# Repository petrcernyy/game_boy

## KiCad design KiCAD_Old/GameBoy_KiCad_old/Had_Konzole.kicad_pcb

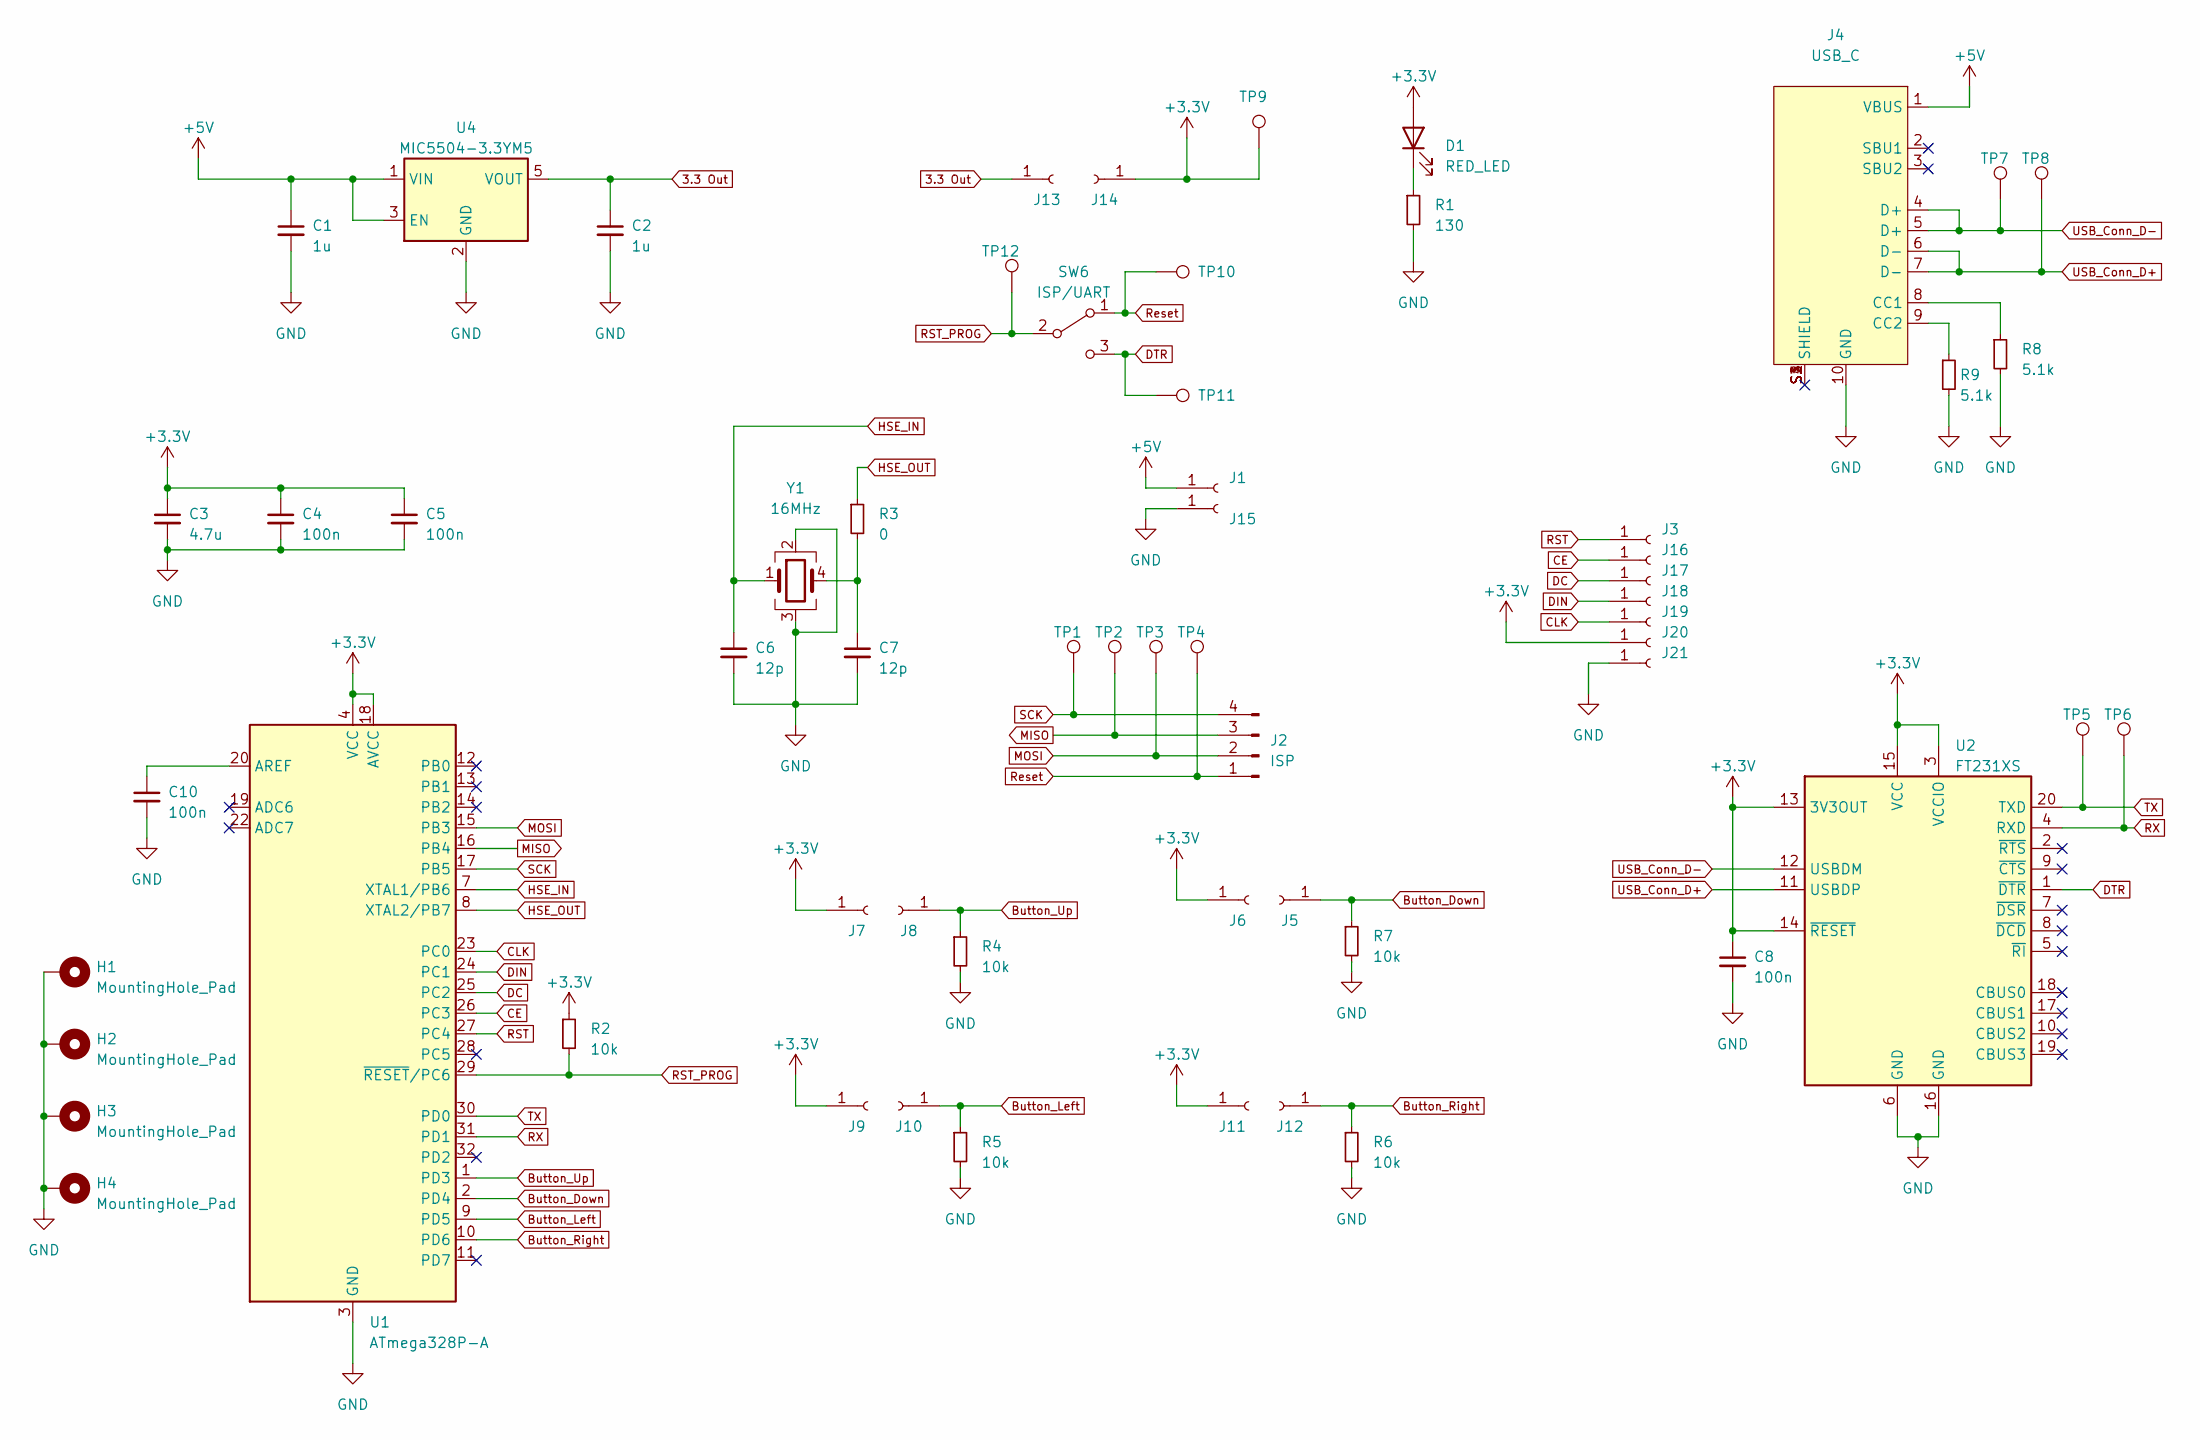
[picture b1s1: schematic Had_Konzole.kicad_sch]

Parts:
C1, C2: 1u; C_0603_1608Metric
C3: 4.7u; C_0603_1608Metric
C4, C5, C8, C10: 100n; C_0603_1608Metric
C6, C7: 12p; C_0603_1608Metric
D1: RED_LED; LED_D5.0mm_Horizontal_O1.27mm_Z3.0mm
H1, H2, H3, H4: MountingHole_Pad; MountingHole_3.2mm_M3_Pad
J1: 5V; TestPoint_Pad_D2.0mm
J2: ISP; Conn_01x04_90
J3: RST; TestPoint_Pad_D2.0mm
J4: USB_C; USB480003A
J5: D; TestPoint_Pad_D2.0mm
J6, J7, J9, J11, J14, J20: 3V3; TestPoint_Pad_D2.0mm
J8: U; TestPoint_Pad_D2.0mm
J10: L; TestPoint_Pad_D2.0mm
J12: R; TestPoint_Pad_D2.0mm
J13: 3V3_O; TestPoint_Pad_D2.0mm
J15, J21: GND; TestPoint_Pad_D2.0mm
J16: CE; TestPoint_Pad_D2.0mm
J17: DC; TestPoint_Pad_D2.0mm
J18: DIN; TestPoint_Pad_D2.0mm
J19: CLK; TestPoint_Pad_D2.0mm
R1: 130; R_0603_1608Metric
R2, R4, R5, R6, R7: 10k; R_0603_1608Metric
R3: 0; R_0603_1608Metric
R8, R9: 5.1k; R_0603_1608Metric
SW6: ISP/UART; SPDT_switch
TP1, TP2, TP3, TP4, TP5, TP6, TP7, TP8, TP9, TP10, TP11, TP12: TestPoint; TestPoint_Pad_D2.0mm
U1: ATmega328P-A; TQFP-32_7x7mm_P0.8mm
U2: FT231XS; SSOP-20_3.9x8.7mm_P0.635mm
U4: MIC5504-3.3YM5; SOT-23-5
Y1: 16MHz; Crystal_SMD_3225-4Pin_3.2x2.5mm

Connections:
3.3 Out: C2.1, J13.1, U4.5 (VOUT)
+3V3: C3.1, C4.1, C5.1, C8.1, D1.2 (A), J6.1, J7.1, J9.1, J11.1, J14.1, J20.1, R2.1, TP9.1, U1.4 (VCC), U1.6 (VCC), U1.18 (AVCC), U2.3 (VCCIO), U2.13 (3V3OUT), U2.14 (~RESET), U2.15 (VCC)
+5V: C1.1, J1.1, J4.1 (VBUS), U4.1 (VIN), U4.3 (EN)
Button_Down: J5.1, R7.1, U1.2 (PD4)
Button_Left: J10.1, R5.1, U1.9 (PD5)
Button_Right: J12.1, R6.1, U1.10 (PD6)
Button_Up: J8.1, R4.1, U1.1 (PD3)
CE: J16.1, U1.26 (PC3)
CLK: J19.1, U1.23 (PC0)
DC: J17.1, U1.25 (PC2)
DIN: J18.1, U1.24 (PC1)
DTR: SW6.3 (C), TP11.1, U2.1 (~DTR)
GND: C1.2, C2.2, C3.2, C4.2, C5.2, C6.2, C7.2, C8.2, C10.2, H1.1, H2.1, H3.1, H4.1, J4.10 (GND), J15.1, J21.1, R1.2, R4.2, R5.2, R6.2, R7.2, R8.2, R9.2, U1.3 (GND), U1.5 (GND), U1.21 (GND), U2.6 (GND), U2.16 (GND), U4.2 (GND), Y1.2, Y1.3
HSE_IN: C6.1, U1.7 (XTAL1/PB6), Y1.1
HSE_OUT: R3.1, U1.8 (XTAL2/PB7)
MISO: J2.3, TP2.1, U1.16 (PB4)
MOSI: J2.2, TP3.1, U1.15 (PB3)
unnamed: C7.1, R3.2, Y1.4
unnamed: D1.1 (K), R1.1
unnamed: J4.8 (CC1), R8.1
unnamed: J4.9 (CC2), R9.1
unnamed: C10.1, U1.20 (AREF)
RST: J3.1, U1.27 (PC4)
RST_PROG: R2.2, SW6.2 (B), TP12.1, U1.29 (~RESET/PC6)
RX: TP6.1, U1.31 (PD1), U2.4 (RXD)
Reset: J2.1, SW6.1 (A), TP4.1, TP10.1
SCK: J2.4, TP1.1, U1.17 (PB5)
TX: TP5.1, U1.30 (PD0), U2.20 (TXD)
USB_Conn_D+: J4.6 (D-), J4.7 (D-), TP8.1, U2.11 (USBDP)
USB_Conn_D-: J4.4 (D+), J4.5 (D+), TP7.1, U2.12 (USBDM)

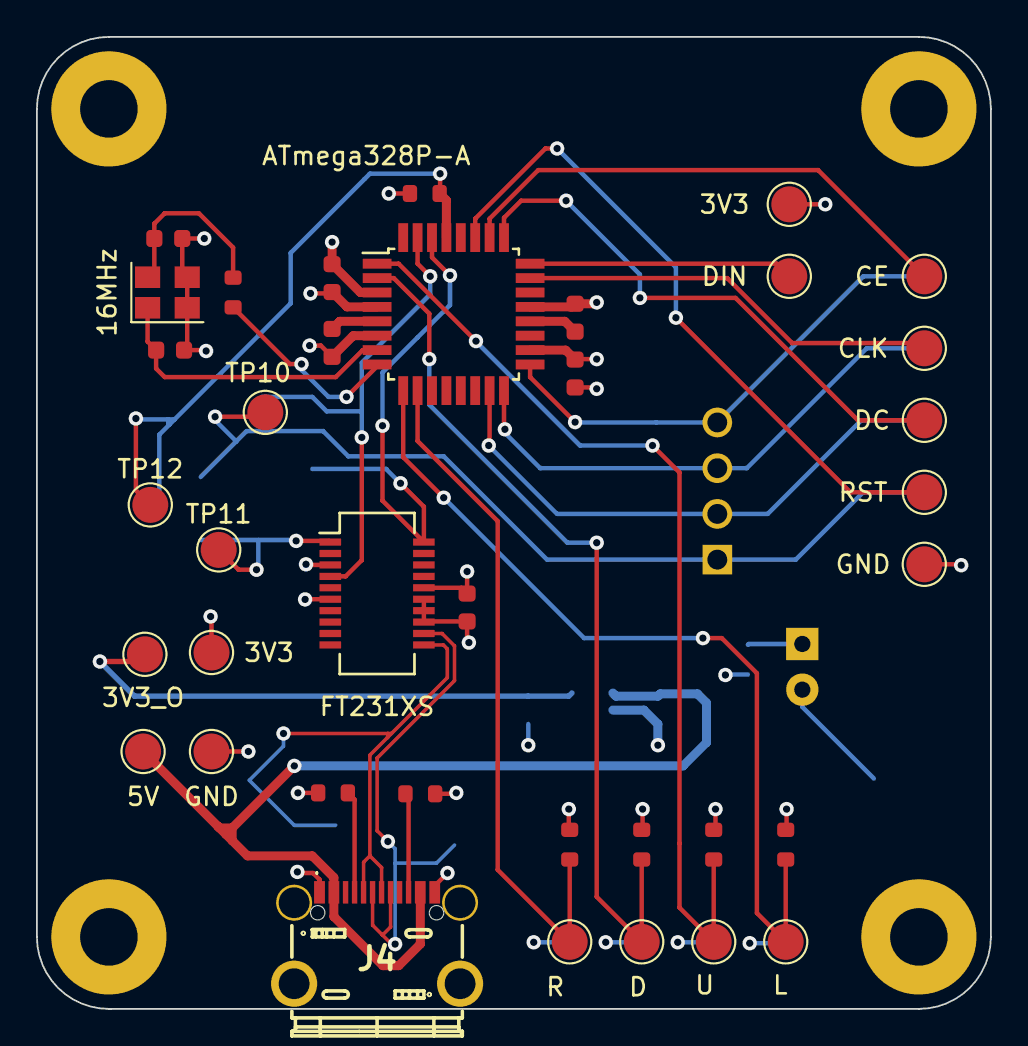
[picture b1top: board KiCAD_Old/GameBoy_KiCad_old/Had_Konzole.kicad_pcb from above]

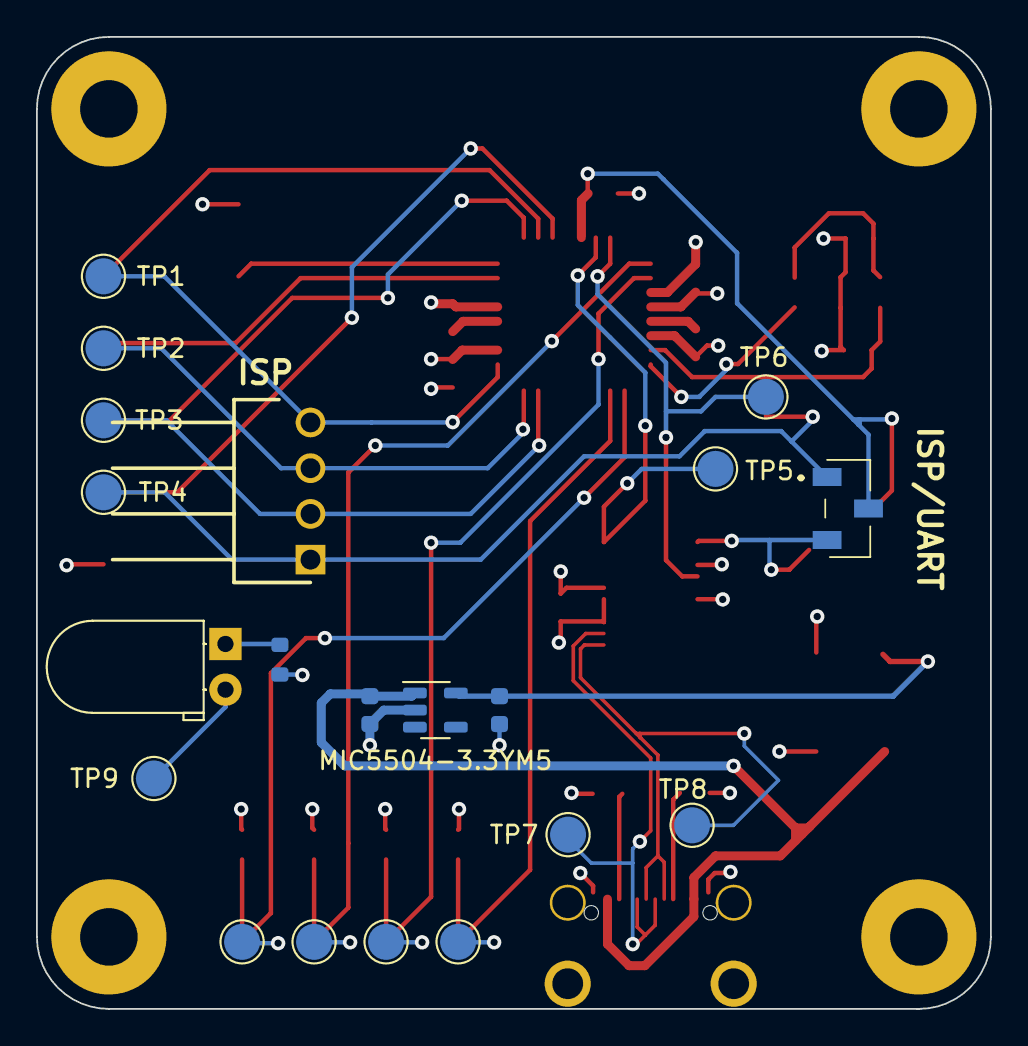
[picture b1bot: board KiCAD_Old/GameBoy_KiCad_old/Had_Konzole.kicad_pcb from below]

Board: 4 copper layers, 53.0 x 54.0 mm, 61 parts (20 on the bottom side), 30 nets.

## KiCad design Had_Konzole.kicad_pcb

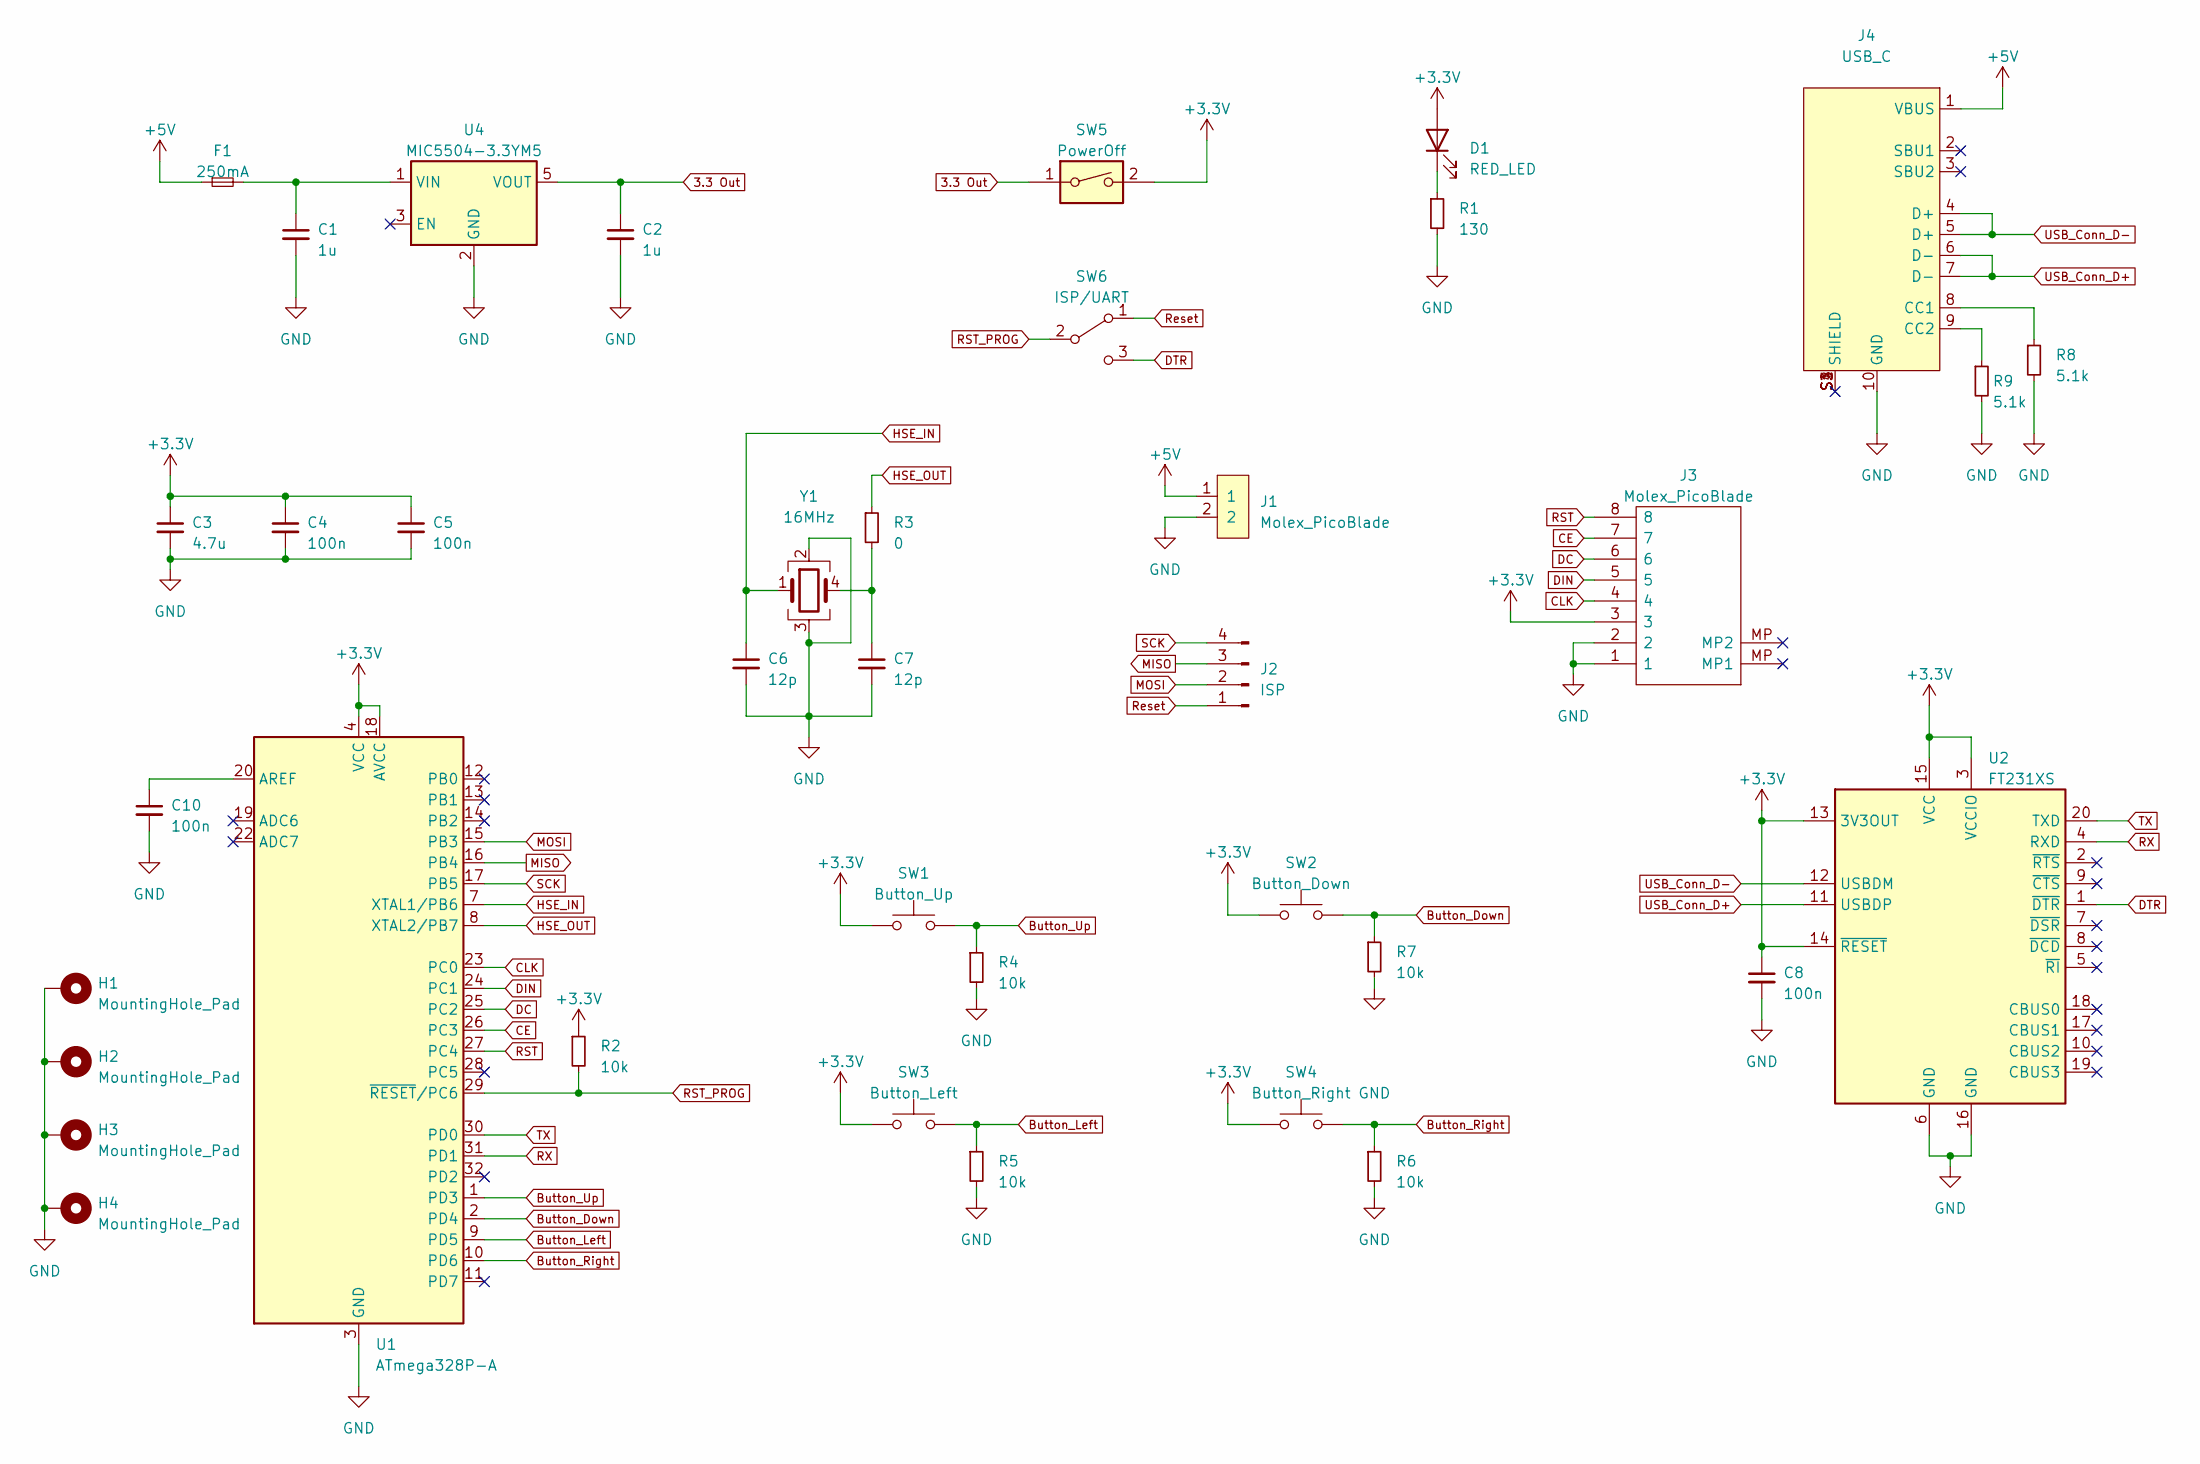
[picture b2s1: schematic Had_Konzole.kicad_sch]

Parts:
C1, C2: 1u; C_0603_1608Metric
C3: 4.7u; C_0603_1608Metric
C4, C5, C8, C10: 100n; C_0603_1608Metric
C6, C7: 12p; C_0603_1608Metric
D1: RED_LED; LED_D5.0mm_Horizontal_O1.27mm_Z3.0mm
F1: 250mA; Fuse_0603_1608Metric
H1, H2, H3, H4: MountingHole_Pad; MountingHole_3.2mm_M3_Pad
J1: Molex_PicoBlade; Molex_PicoBlade_53261-0271_1x02-1MP_P1.25mm_Horizontal
J2: ISP; Conn_01x04_90
J3: Molex_PicoBlade; Molex_PicoBlade_53261-0871_1x08-1MP_P1.25mm_Horizontal; Manufacturer_Part_Number 53261-0671
J4: USB_C; MOLEX_2171790001
R1: 130; R_0603_1608Metric
R2, R4, R5, R6, R7: 10k; R_0603_1608Metric
R3: 0; R_0603_1608Metric
R8, R9: 5.1k; R_0603_1608Metric
SW1: Button_Up; Tactile_switch
SW2: Button_Down; Tactile_switch
SW3: Button_Left; Tactile_switch
SW4: Button_Right; Tactile_switch
SW5: PowerOff; DS04254101BKSMT
SW6: ISP/UART; SPDT_switch
U1: ATmega328P-A; TQFP-32_7x7mm_P0.8mm
U2: FT231XS; SSOP-20_3.9x8.7mm_P0.635mm
U4: MIC5504-3.3YM5; SOT-23-5
Y1: 16MHz; Crystal_SMD_3225-4Pin_3.2x2.5mm

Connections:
3.3 Out: C2.1, SW5.1, U4.5 (VOUT)
+3V3: C3.1, C4.1, C5.1, C8.1, D1.2 (A), J3.3, R2.1, SW1.1, SW2.1, SW3.1, SW4.1, SW5.2, U1.4 (VCC), U1.6 (VCC), U1.18 (AVCC), U2.3 (VCCIO), U2.13 (3V3OUT), U2.14 (~RESET), U2.15 (VCC)
+5V: F1.1, J1.1, J4.1 (VBUS)
Button_Down: R7.1, SW2.2, U1.2 (PD4)
Button_Left: R5.1, SW3.2, U1.9 (PD5)
Button_Right: R6.1, SW4.2, U1.10 (PD6)
Button_Up: R4.1, SW1.2, U1.1 (PD3)
CE: J3.7, U1.26 (PC3)
CLK: J3.4, U1.23 (PC0)
DC: J3.6, U1.25 (PC2)
DIN: J3.5, U1.24 (PC1)
DTR: SW6.3 (C), U2.1 (~DTR)
GND: C1.2, C2.2, C3.2, C4.2, C5.2, C6.2, C7.2, C8.2, C10.2, H1.1, H2.1, H3.1, H4.1, J1.2, J3.1, J3.2, J4.10 (GND), R1.2, R4.2, R5.2, R6.2, R7.2, R8.2, R9.2, U1.3 (GND), U1.5 (GND), U1.21 (GND), U2.6 (GND), U2.16 (GND), U4.2 (GND), Y1.2, Y1.3
HSE_IN: C6.1, U1.7 (XTAL1/PB6), Y1.1
HSE_OUT: R3.1, U1.8 (XTAL2/PB7)
MISO: J2.3, U1.16 (PB4)
MOSI: J2.2, U1.15 (PB3)
unnamed: C7.1, R3.2, Y1.4
unnamed: D1.1 (K), R1.1
unnamed: J4.8 (CC1), R8.1
unnamed: J4.9 (CC2), R9.1
unnamed: C10.1, U1.20 (AREF)
unnamed: C1.1, F1.2, U4.1 (VIN)
RST: J3.8, U1.27 (PC4)
RST_PROG: R2.2, SW6.2 (B), U1.29 (~RESET/PC6)
RX: U1.31 (PD1), U2.4 (RXD)
Reset: J2.1, SW6.1 (A)
SCK: J2.4, U1.17 (PB5)
TX: U1.30 (PD0), U2.20 (TXD)
USB_Conn_D+: J4.6 (D-), J4.7 (D-), U2.11 (USBDP)
USB_Conn_D-: J4.4 (D+), J4.5 (D+), U2.12 (USBDM)

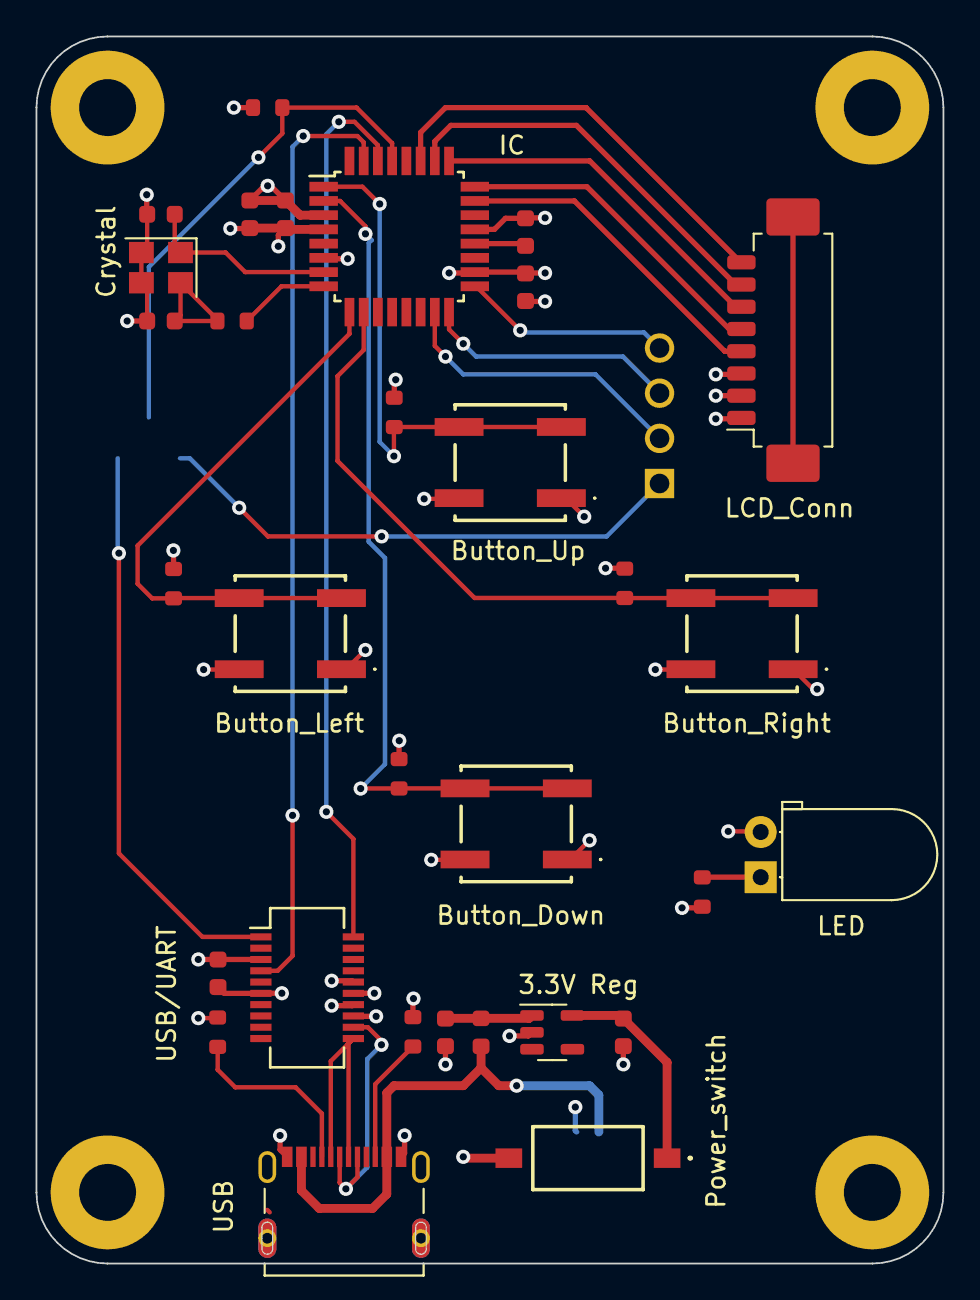
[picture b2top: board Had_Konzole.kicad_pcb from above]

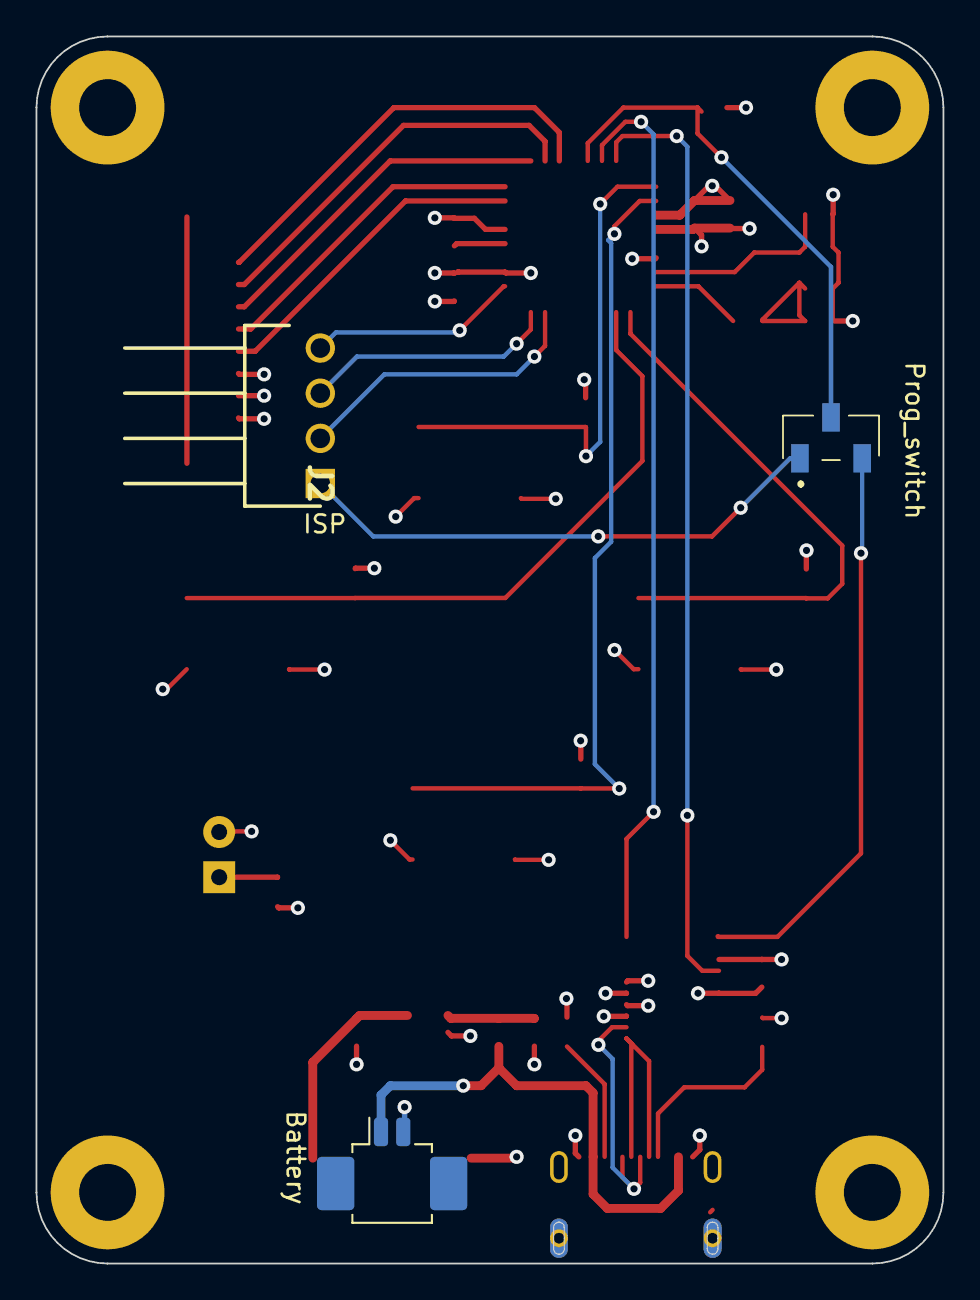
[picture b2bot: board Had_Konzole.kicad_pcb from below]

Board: 4 copper layers, 51.0 x 69.0 mm, 38 parts (3 on the bottom side), 31 nets.

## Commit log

2023-09-02 Update PCB v2.0, switch to Altium, added Firmware and 3D model of enclosure
2023-09-27 Delete
2023-09-27 Added Altium PCB
